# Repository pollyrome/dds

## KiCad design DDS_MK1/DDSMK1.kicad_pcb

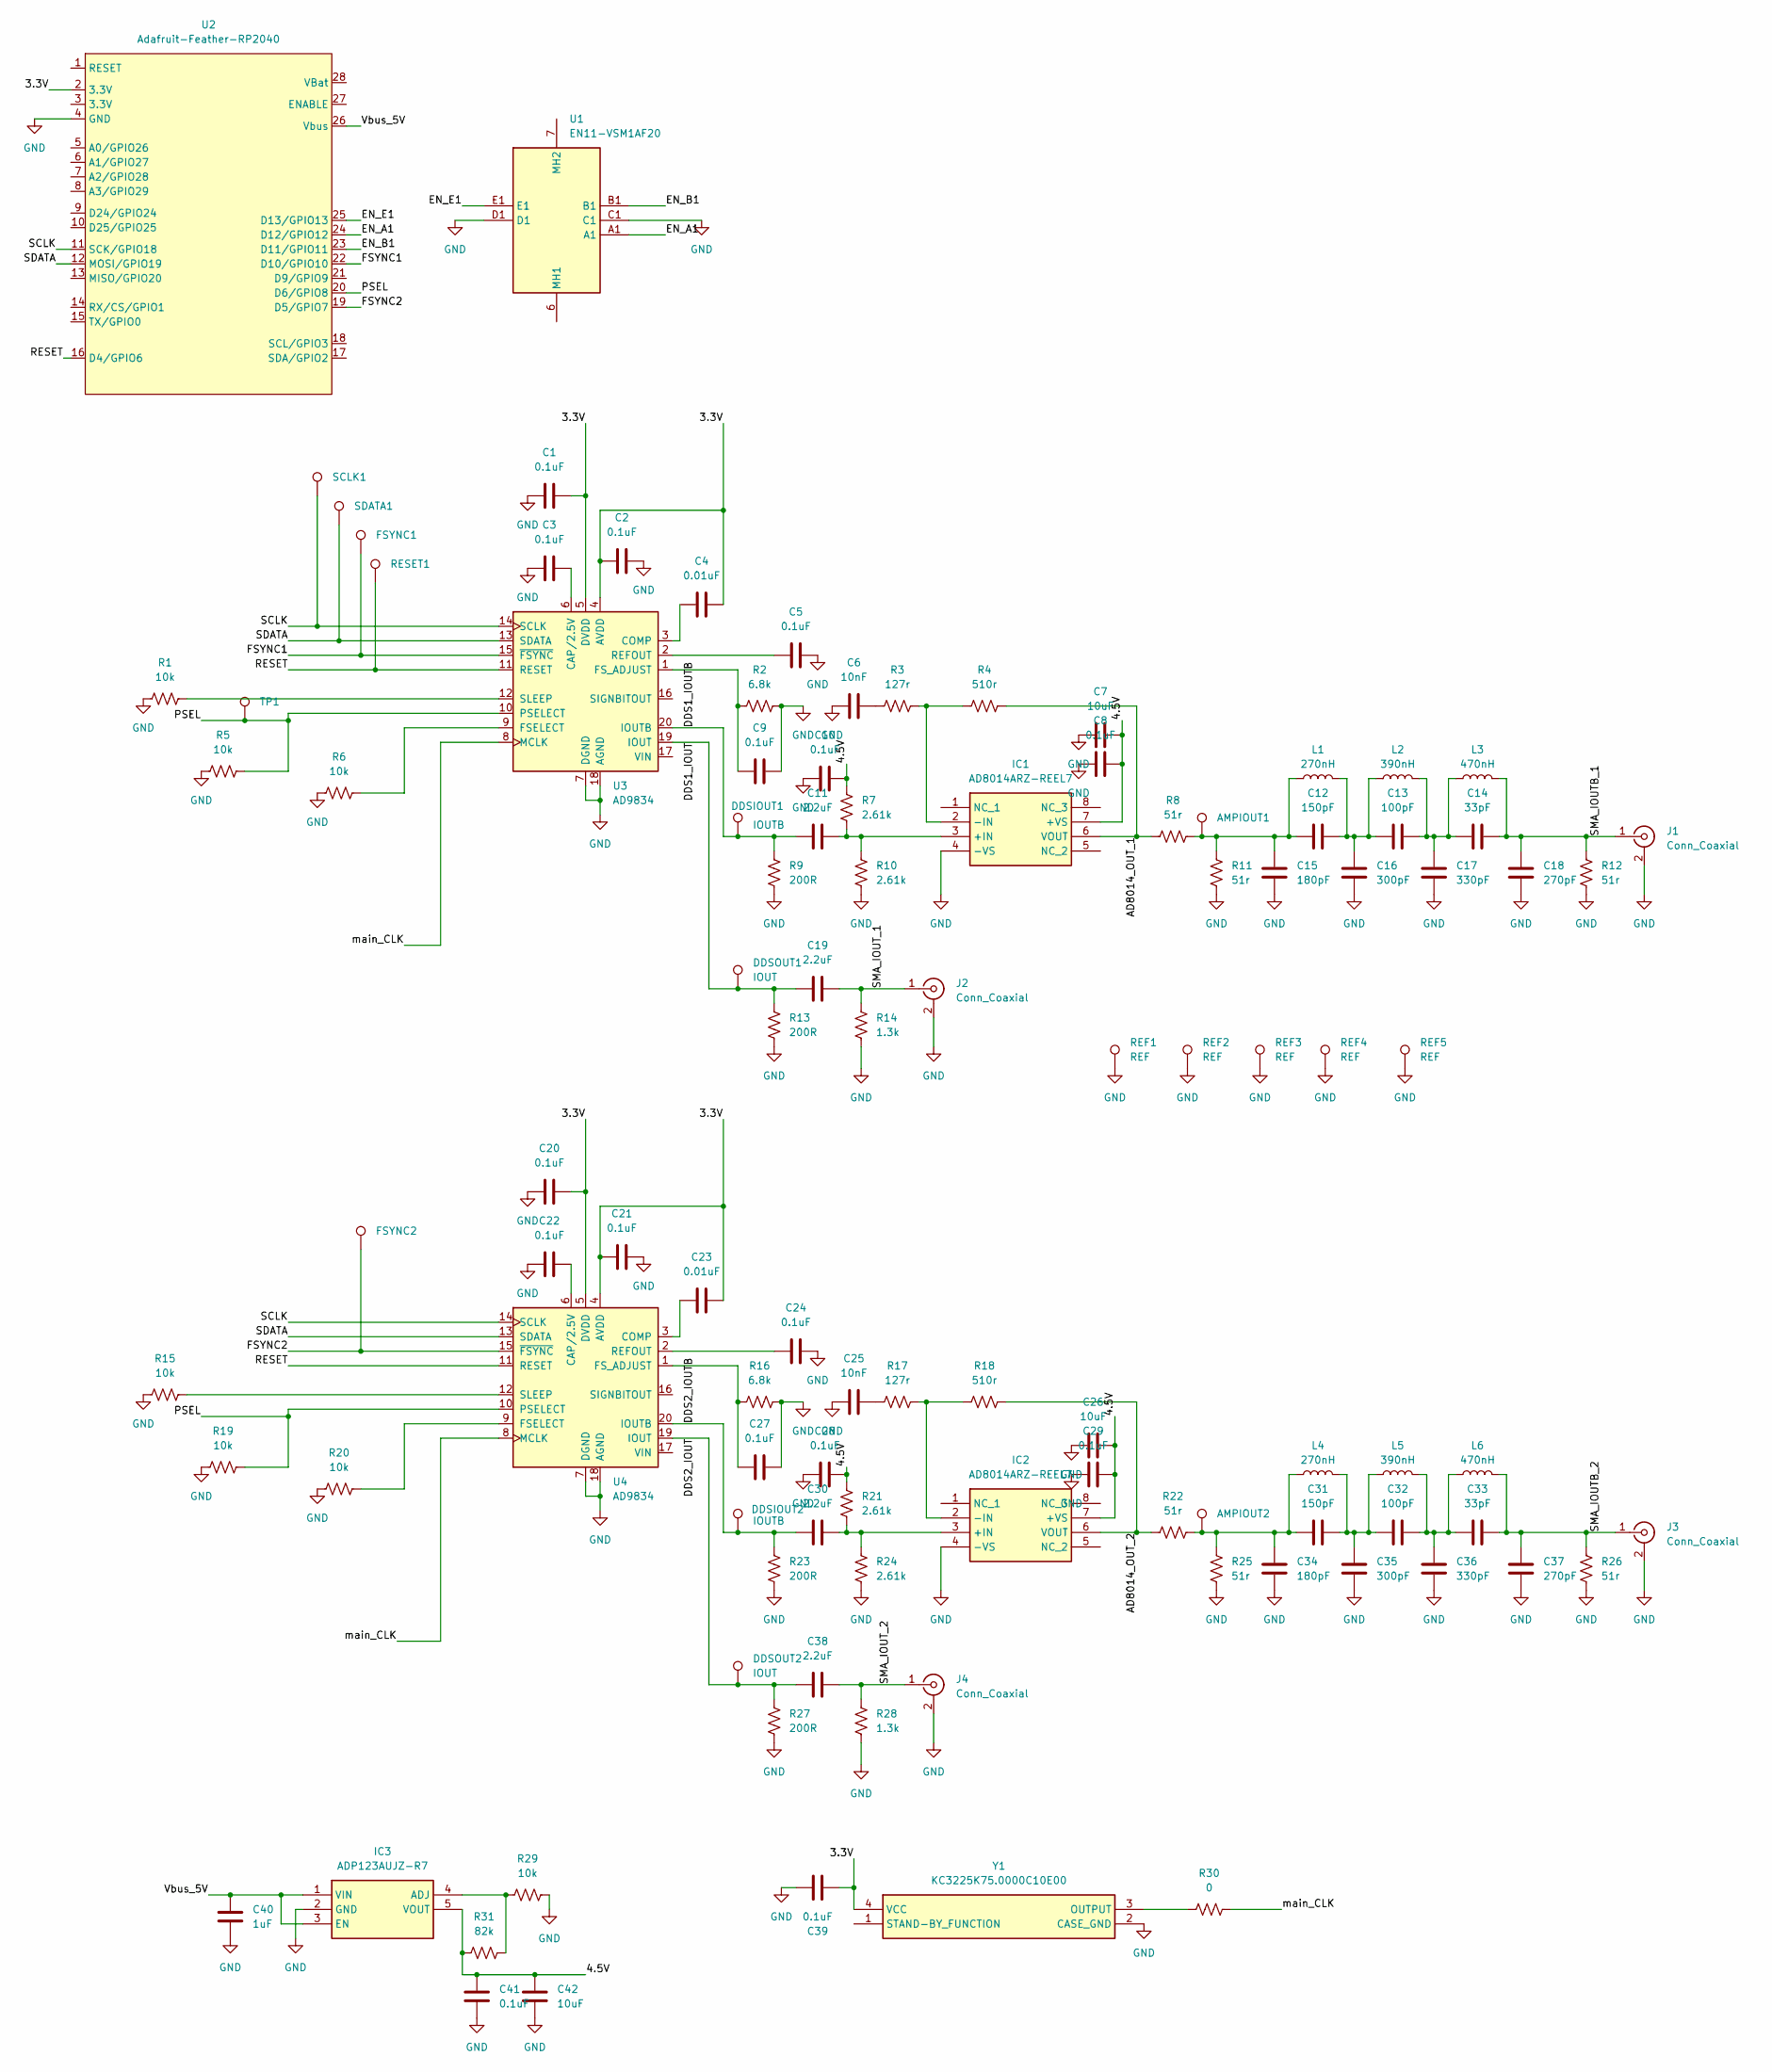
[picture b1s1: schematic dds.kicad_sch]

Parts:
AMPIOUT1, AMPIOUT2: 5010
C1, C2, C3, C5, C8, C9, C10, C20, C21, C22, C24, C27, C28, C29, C39, C41: 0.1uF; C_1206_3216Metric_Pad1.33x1.80mm_HandSolder
C4, C23: 0.01uF; C_1206_3216Metric_Pad1.33x1.80mm_HandSolder
C6, C25: 10nF; C_1206_3216Metric_Pad1.33x1.80mm_HandSolder
C7, C26, C42: 10uF; C_1206_3216Metric_Pad1.33x1.80mm_HandSolder
C11, C19, C30, C38: 2.2uF; C_1206_3216Metric_Pad1.33x1.80mm_HandSolder
C12, C31: 150pF; C_1206_3216Metric_Pad1.33x1.80mm_HandSolder
C13, C32: 100pF; C_1206_3216Metric_Pad1.33x1.80mm_HandSolder
C14, C33: 33pF; C_1206_3216Metric_Pad1.33x1.80mm_HandSolder
C15, C34: 180pF; C_1206_3216Metric_Pad1.33x1.80mm_HandSolder
C16, C35: 300pF; C_1206_3216Metric_Pad1.33x1.80mm_HandSolder
C17, C36: 330pF; C_1206_3216Metric_Pad1.33x1.80mm_HandSolder
C18, C37: 270pF; C_1206_3216Metric_Pad1.33x1.80mm_HandSolder
C40: 1uF; C_1206_3216Metric_Pad1.33x1.80mm_HandSolder
DDSIOUT1, DDSIOUT2: IOUTB; TestPoint_Keystone_5000-5004_Miniature
DDSOUT1, DDSOUT2: IOUT; TestPoint_Keystone_5000-5004_Miniature
FSYNC1, FSYNC2: 5010
IC1, IC2: AD8014ARZ-REEL7; SOIC127P600X175-8N; Manufacturer_Part_Number AD8014ARZ-REEL7; Mouser Part Number 584-AD8014ARZ-R7
IC3: ADP123AUJZ-R7; SOT95P280X100-5N; Mouser Part Number 584-ADP123AUJZ-R7
J1, J2, J3, J4: Conn_Coaxial; SMA_Molex_73251-2120_EdgeMount_Horizontal
L1, L4: 270nH; L_1206_3216Metric_Pad1.22x1.90mm_HandSolder
L2, L5: 390nH; L_1206_3216Metric_Pad1.22x1.90mm_HandSolder
L3, L6: 470nH; L_1206_3216Metric_Pad1.22x1.90mm_HandSolder
R1, R5, R6, R15, R19, R20, R29: 10k; R_1206_3216Metric_Pad1.30x1.75mm_HandSolder
R2, R16: 6.8k; R_1206_3216Metric_Pad1.30x1.75mm_HandSolder
R3, R17: 127r; R_1206_3216Metric_Pad1.30x1.75mm_HandSolder
R4, R18: 510r; R_1206_3216Metric_Pad1.30x1.75mm_HandSolder
R7, R10, R21, R24: 2.61k; R_1206_3216Metric_Pad1.30x1.75mm_HandSolder
R8, R11, R12, R22, R25, R26: 51r; R_1206_3216Metric_Pad1.30x1.75mm_HandSolder
R9, R13, R23, R27: 200R; R_1206_3216Metric_Pad1.30x1.75mm_HandSolder
R14, R28: 1.3k; R_1206_3216Metric_Pad1.30x1.75mm_HandSolder
R30: 0; R_1206_3216Metric_Pad1.30x1.75mm_HandSolder
R31: 82k; R_1206_3216Metric_Pad1.30x1.75mm_HandSolder
REF1, REF2, REF3, REF4, REF5: REF; 5010
RESET1: 5010
SCLK1: 5010
SDATA1: 5010
TP1: 5010
U1: EN11-VSM1AF20; EN11VSM1AF20; Mouser Part Number 858-EN11-VSM1AF20
U2: Adafruit-Feather-RP2040
U3, U4: AD9834; TSSOP-20_4.4x6.5mm_P0.65mm
Y1: KC3225K75.0000C10E00; KC3225K750000C10E00; Mouser Part Number 581-KC3225K75.0C10E

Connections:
/3.3V: C1.2, C2.1, C4.2, C20.2, C21.1, C23.2, C39.1, U2.2 (3.3V), U3.4 (AVDD), U3.5 (DVDD), U4.4 (AVDD), U4.5 (DVDD), Y1.4 (VCC)
/4.5V: C7.1, C8.1, C10.2, C26.1, C28.2, C29.1, C41.1, C42.1, IC1.7 (+VS), IC2.7 (+VS), IC3.5 (VOUT), R7.2, R21.2, R31.1
/AD8014_OUT_1: IC1.6 (VOUT), R4.2, R8.1
/AD8014_OUT_2: IC2.6 (VOUT), R18.2, R22.1
/DDS1_IOUT: C19.1, DDSOUT1.1 (1_1), R13.2, U3.19 (IOUT)
/DDS1_IOUTB: C11.1, DDSIOUT1.1 (1_1), R9.2, U3.20 (IOUTB)
/DDS2_IOUT: C38.1, DDSOUT2.1 (1_1), R27.2, U4.19 (IOUT)
/DDS2_IOUTB: C30.1, DDSIOUT2.1 (1_1), R23.2, U4.20 (IOUTB)
/EN_A1: U1.A1, U2.24 (D12/GPIO12)
/EN_B1: U1.B1, U2.23 (D11/GPIO11)
/EN_E1: U1.E1, U2.25 (D13/GPIO13)
/FSYNC1: FSYNC1.1 (1_1), U2.22 (D10/GPIO10), U3.15 (~FSYNC)
/FSYNC2: FSYNC2.1 (1_1), U2.19 (D5/GPIO7), U4.15 (~FSYNC)
/PSEL: R5.2, R19.2, TP1.1 (1_1), U2.20 (D6/GPIO8), U3.10 (PSELECT), U4.10 (PSELECT)
/RESET: RESET1.1 (1_1), U2.16 (D4/GPIO6), U3.11 (RESET), U4.11 (RESET)
/SCLK: SCLK1.1 (1_1), U2.11 (SCK/GPIO18), U3.14 (SCLK), U4.14 (SCLK)
/SDATA: SDATA1.1 (1_1), U2.12 (MOSI/GPIO19), U3.13 (SDATA), U4.13 (SDATA)
/SMA_IOUTB_1: C14.1, C18.2, J1.1 (In), L3.2, R12.2
/SMA_IOUTB_2: C33.1, C37.2, J3.1 (In), L6.2, R26.2
/SMA_IOUT_1: C19.2, J2.1 (In), R14.2
/SMA_IOUT_2: C38.2, J4.1 (In), R28.2
/Vbus_5V: C40.1, IC3.1 (VIN), IC3.3 (EN), U2.26 (Vbus)
/main_CLK: R30.1, U3.8 (MCLK), U4.8 (MCLK)
GND: C1.1, C2.2, C3.1, C5.2, C6.1, C7.2, C8.2, C9.2, C10.1, C15.1, C16.1, C17.1, C18.1, C20.1, C21.2, C22.1, C24.2, C25.1, C26.2, C27.2, C28.1, C29.2, C34.1, C35.1, C36.1, C37.1, C39.2, C40.2, C41.2, C42.2, IC1.4 (-VS), IC2.4 (-VS), IC3.2 (GND), J1.2 (Ext), J2.2 (Ext), J3.2 (Ext), J4.2 (Ext), R1.1, R2.2, R5.1, R6.1, R9.1, R10.1, R11.1, R12.1, R13.1, R14.1, R15.1, R16.2, R19.1, R20.1, R23.1, R24.1, R25.1, R26.1, R27.1, R28.1, R29.2, REF1.1 (1_1), REF2.1 (1_1), REF3.1 (1_1), REF4.1 (1_1), REF5.1 (1_1), U1.C1, U1.D1, U2.4 (GND), U3.7 (DGND), U3.18 (AGND), U4.7 (DGND), U4.18 (AGND), Y1.2 (CASE_GND)
unnamed: AMPIOUT1.1 (1_1), C12.2, C15.2, L1.1, R8.2, R11.2
unnamed: AMPIOUT2.1 (1_1), C31.2, C34.2, L4.1, R22.2, R25.2
unnamed: C6.2, R3.1
unnamed: C12.1, C13.2, C16.2, L1.2, L2.1
unnamed: C13.1, C14.2, C17.2, L2.2, L3.1
unnamed: C25.2, R17.1
unnamed: C31.1, C32.2, C35.2, L4.2, L5.1
unnamed: C32.1, C33.2, C36.2, L5.2, L6.1
unnamed: C11.2, IC1.3 (+IN), R7.1, R10.2
unnamed: IC1.2 (-IN), R3.2, R4.1
unnamed: C30.2, IC2.3 (+IN), R21.1, R24.2
unnamed: IC2.2 (-IN), R17.2, R18.1
unnamed: IC3.4 (ADJ), R29.1, R31.2
unnamed: C3.2, U3.6 (CAP/2.5V)
unnamed: C4.1, U3.3 (COMP)
unnamed: R6.2, U3.9 (FSELECT)
unnamed: C9.1, R2.1, U3.1 (FS_ADJUST)
unnamed: C5.1, U3.2 (REFOUT)
unnamed: R1.2, U3.12 (SLEEP)
unnamed: C22.2, U4.6 (CAP/2.5V)
unnamed: C23.1, U4.3 (COMP)
unnamed: R20.2, U4.9 (FSELECT)
unnamed: C27.1, R16.1, U4.1 (FS_ADJUST)
unnamed: C24.1, U4.2 (REFOUT)
unnamed: R15.2, U4.12 (SLEEP)
unnamed: R30.2, Y1.3 (OUTPUT)

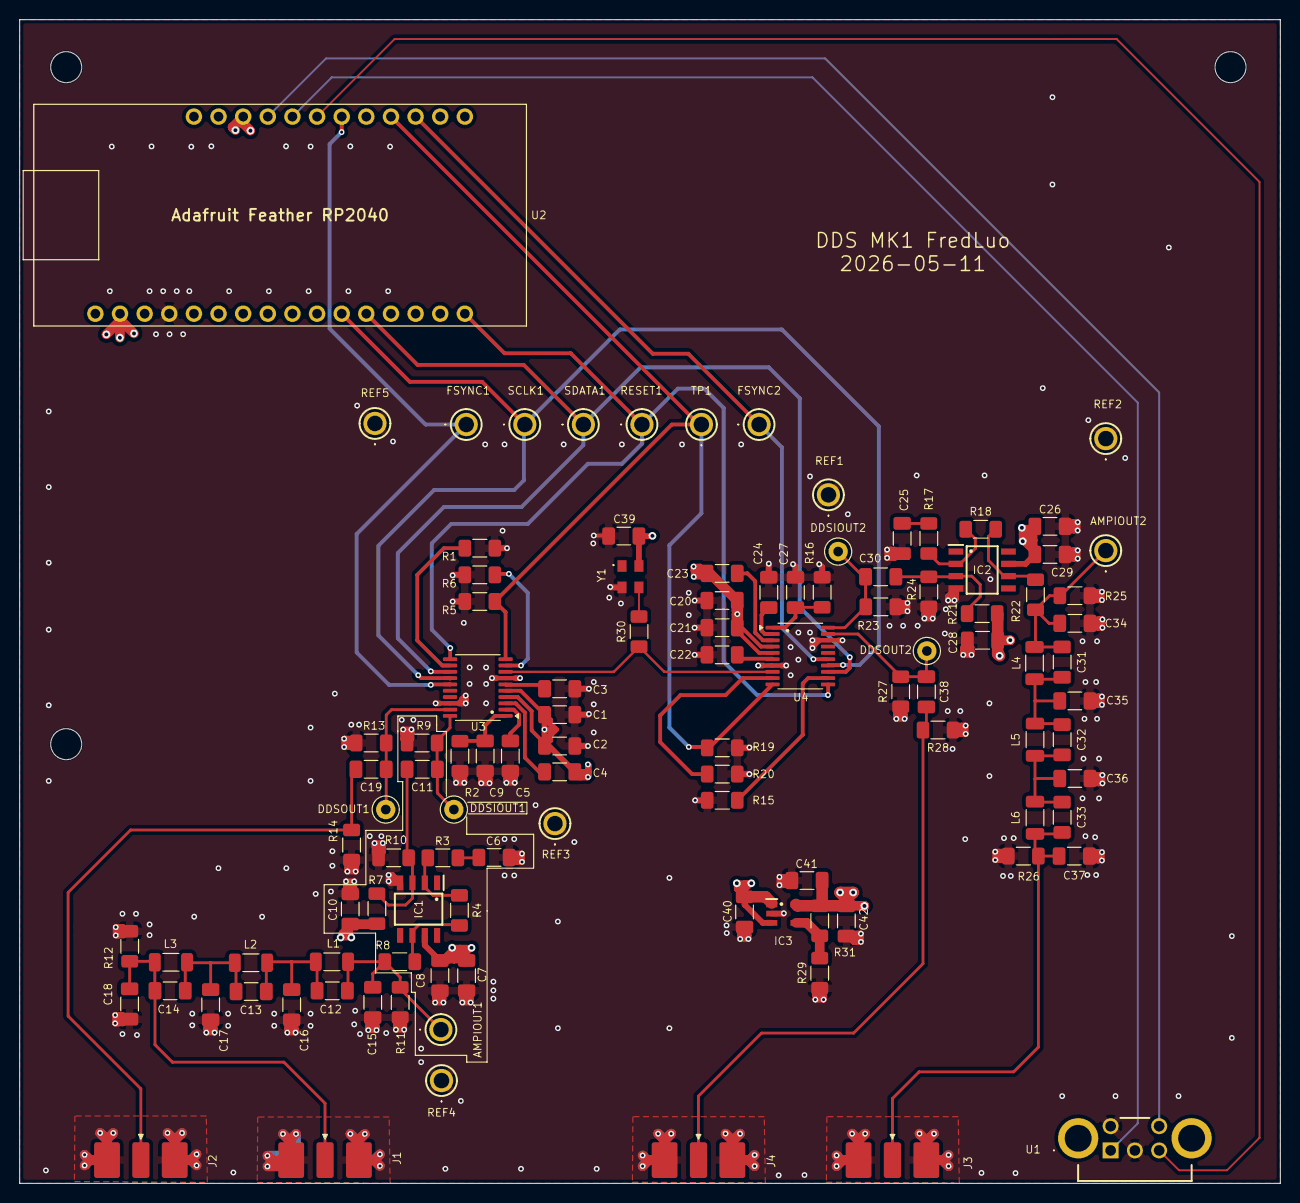
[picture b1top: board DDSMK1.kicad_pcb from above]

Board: 4 copper layers, 130.0 x 120.0 mm, 108 parts (0 on the bottom side), 50 nets.

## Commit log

2026-05-11 Added DDSMK1 files
